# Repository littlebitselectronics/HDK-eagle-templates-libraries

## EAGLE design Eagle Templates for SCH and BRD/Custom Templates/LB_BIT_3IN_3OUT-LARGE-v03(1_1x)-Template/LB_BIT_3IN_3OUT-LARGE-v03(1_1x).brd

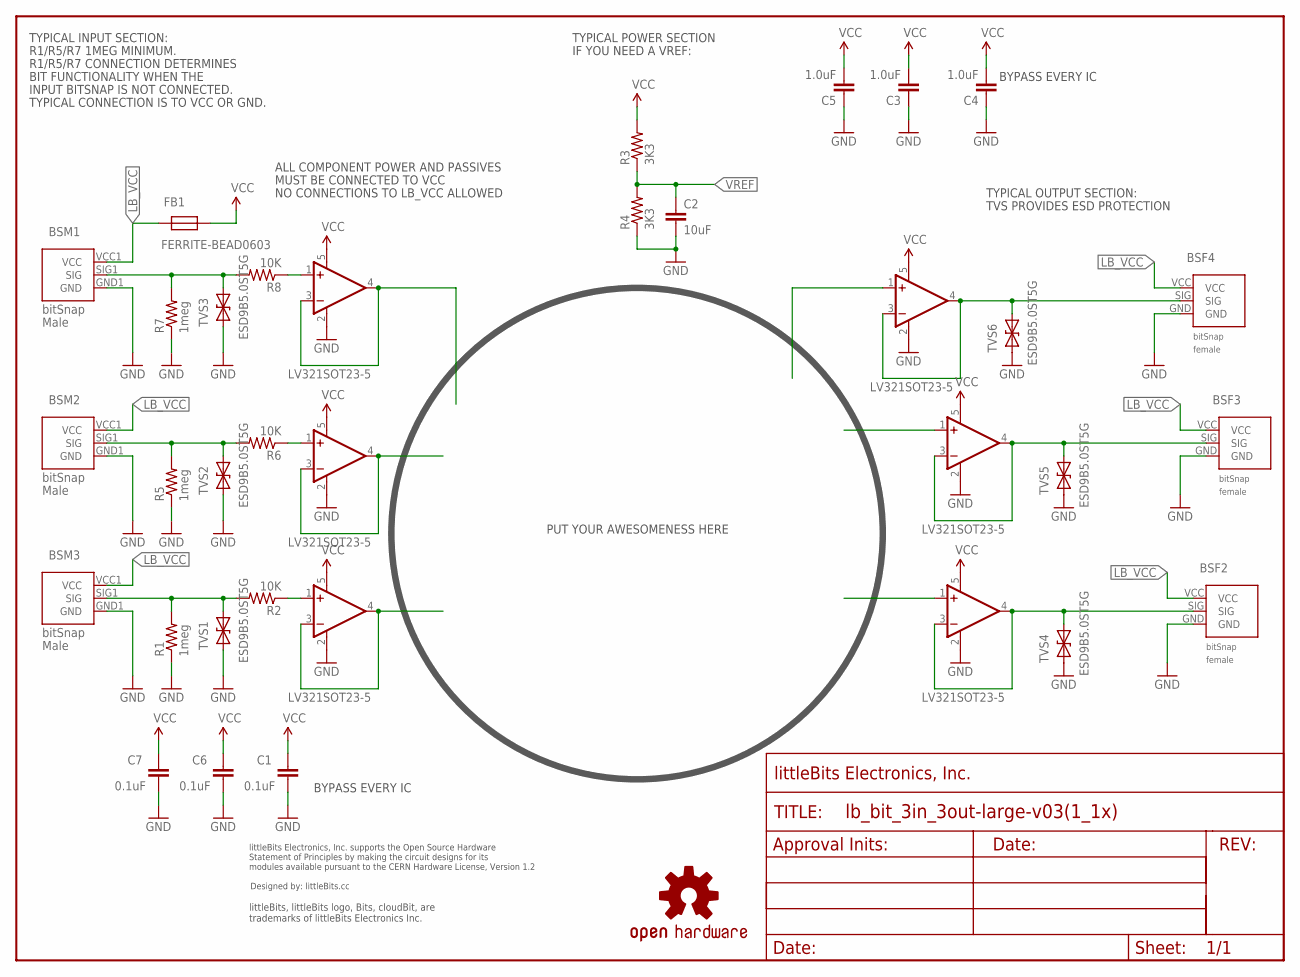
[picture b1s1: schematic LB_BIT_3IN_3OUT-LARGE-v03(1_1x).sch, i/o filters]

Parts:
BSF2, BSF3, BSF4: BITSNAP_V03_FEMALE
BSM1, BSM2, BSM3: BITSNAP_V03_MALE
C1, C6, C7: 0.1uF; CAP-0603
C2: 10uF; CAP-0603
C3, C4, C5: 1.0uF; CAP-0603
FB1: FERRITE-BEAD0603; R0603
FRAME1: FRAME-LETTER; FABDWG01-OHW
R1, R5, R7: 1meg; RES-0603
R2, R6, R8: 10K; RES-0603
R3, R4: 3K3; RES-0603
TVS1, TVS2, TVS3, TVS4, TVS5, TVS6: ESD9B5.0ST5G; SOD-923
U1, U2, U3, U4, U5, U6: LV321SOT23-5; SOT23-5
U$1: OSHWCREDIT
U$70: OSHW-LOGOL; OSHW-LOGO-L

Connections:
GND: BSF2.GND, BSF3.GND, BSF4.GND, BSM1.GND1 (GND), BSM2.GND1 (GND), BSM3.GND1 (GND), C1.2, C2.2, C3.1, C4.1, C5.1, C6.2, C7.2, R1.1, R4.1, R5.1, R7.1, TVS1.1 (A), TVS2.1 (A), TVS3.1 (A), TVS4.1 (A), TVS5.1 (A), TVS6.1 (A), U1.2 (V-), U2.2 (V-), U3.2 (V-), U4.2 (V-), U5.2 (V-), U6.2 (V-)
LB_VCC: BSF2.VCC, BSF3.VCC, BSF4.VCC, BSM1.VCC1 (VCC), BSM2.VCC1 (VCC), BSM3.VCC1 (VCC), FB1.2
unnamed: R2.1, U1.1 (+IN)
unnamed: U1.3 (-IN), U1.4 (OUT)
unnamed: BSM1.SIG1 (SIG), R7.2, R8.2, TVS3.2 (C)
unnamed: BSM2.SIG1 (SIG), R5.2, R6.2, TVS2.2 (C)
unnamed: BSM3.SIG1 (SIG), R1.2, R2.2, TVS1.2 (C)
unnamed: U2.3 (-IN), U2.4 (OUT)
unnamed: R6.1, U2.1 (+IN)
unnamed: U3.3 (-IN), U3.4 (OUT)
unnamed: R8.1, U3.1 (+IN)
SIG_OUT1: BSF4.SIG, TVS6.2 (C), U6.3 (-IN), U6.4 (OUT)
SIG_OUT2: BSF3.SIG, TVS5.2 (C), U5.3 (-IN), U5.4 (OUT)
SIG_OUT3: BSF2.SIG, TVS4.2 (C), U4.3 (-IN), U4.4 (OUT)
VCC: C1.1, C3.2, C4.2, C5.2, C6.1, C7.1, FB1.1, R3.2, U1.5 (V+), U2.5 (V+), U3.5 (V+), U4.5 (V+), U5.5 (V+), U6.5 (V+)
VREF: C2.1, R3.1, R4.2

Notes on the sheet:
R1/R5/R7 1MEG MINIMUM.
R1/R5/R7 CONNECTION DETERMINES
BIT FUNCTIONALITY WHEN THE
INPUT BITSNAP IS NOT CONNECTED.
TYPICAL CONNECTION IS TO VCC OR GND.
TYPICAL INPUT SECTION:
TYPICAL POWER SECTION
IF YOU NEED A VREF:
PUT YOUR AWESOMENESS HERE
TYPICAL OUTPUT SECTION:
BYPASS EVERY IC
NO CONNECTIONS TO LB_VCC ALLOWED
ALL COMPONENT POWER AND PASSIVES
MUST BE CONNECTED TO VCC
TVS PROVIDES ESD PROTECTION

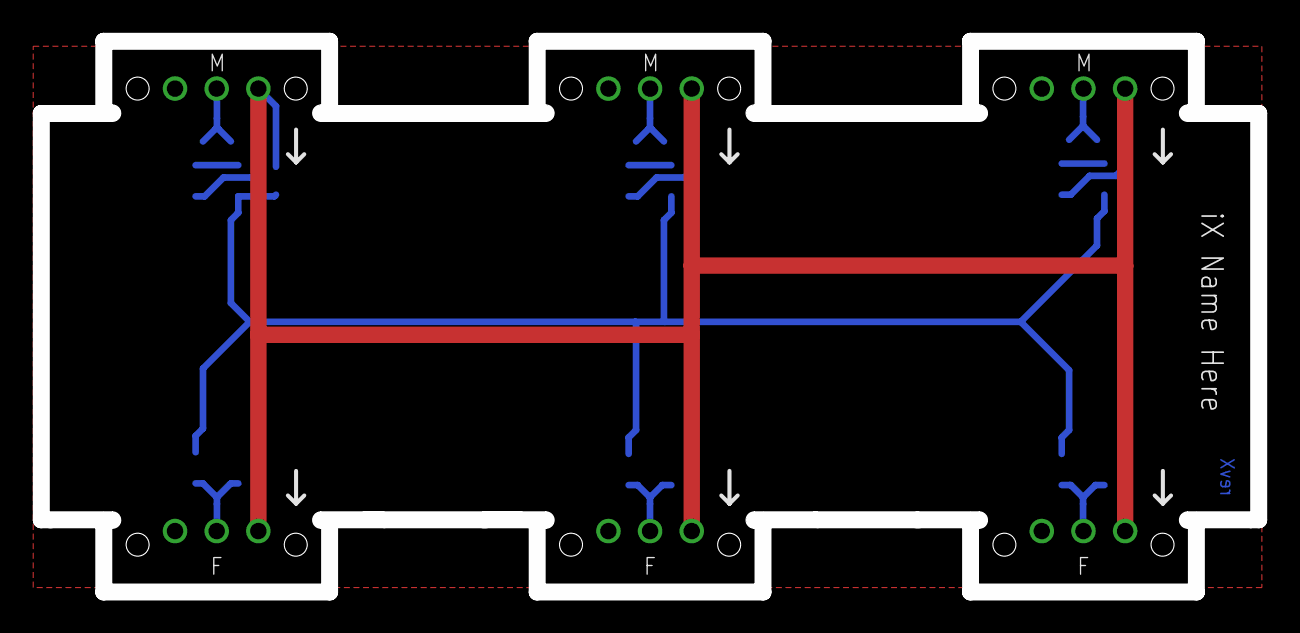
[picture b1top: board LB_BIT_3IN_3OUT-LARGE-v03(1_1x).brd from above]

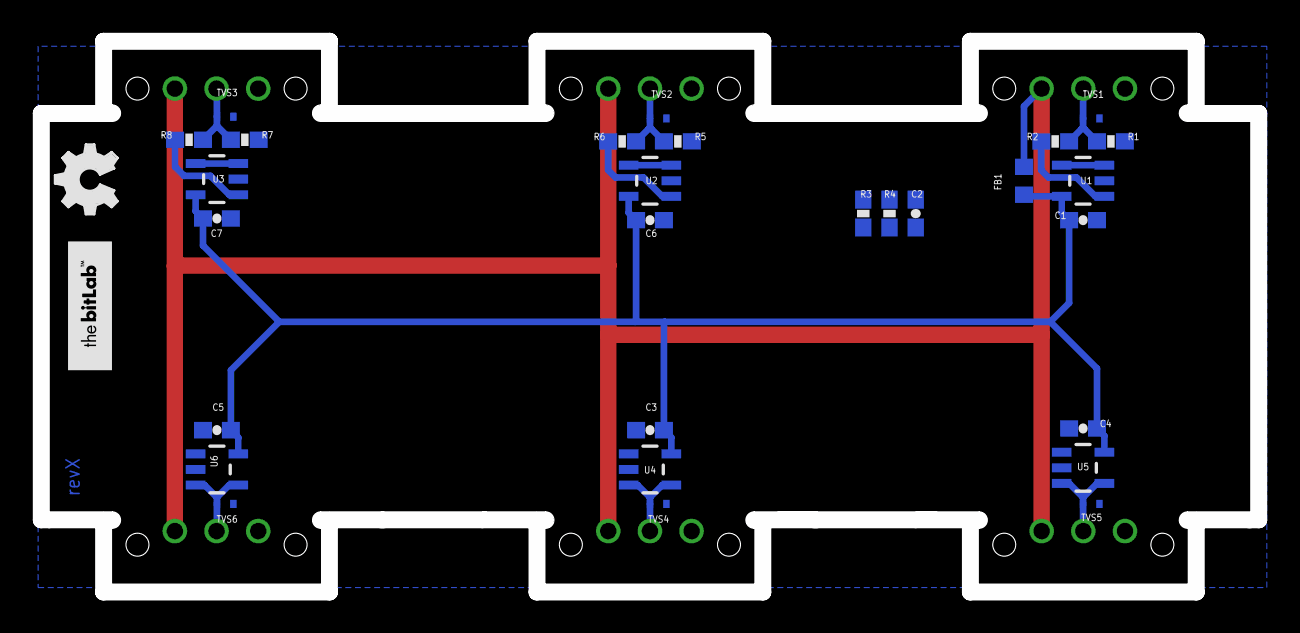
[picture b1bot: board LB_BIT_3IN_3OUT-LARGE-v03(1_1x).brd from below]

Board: 2 copper layers, 74.2 x 33.6 mm, 39 parts (28 on the bottom side), 16 nets.

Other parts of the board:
U$2: BITLAB-LOGO
U$5: OSHW_FILLX150_NOTEXT

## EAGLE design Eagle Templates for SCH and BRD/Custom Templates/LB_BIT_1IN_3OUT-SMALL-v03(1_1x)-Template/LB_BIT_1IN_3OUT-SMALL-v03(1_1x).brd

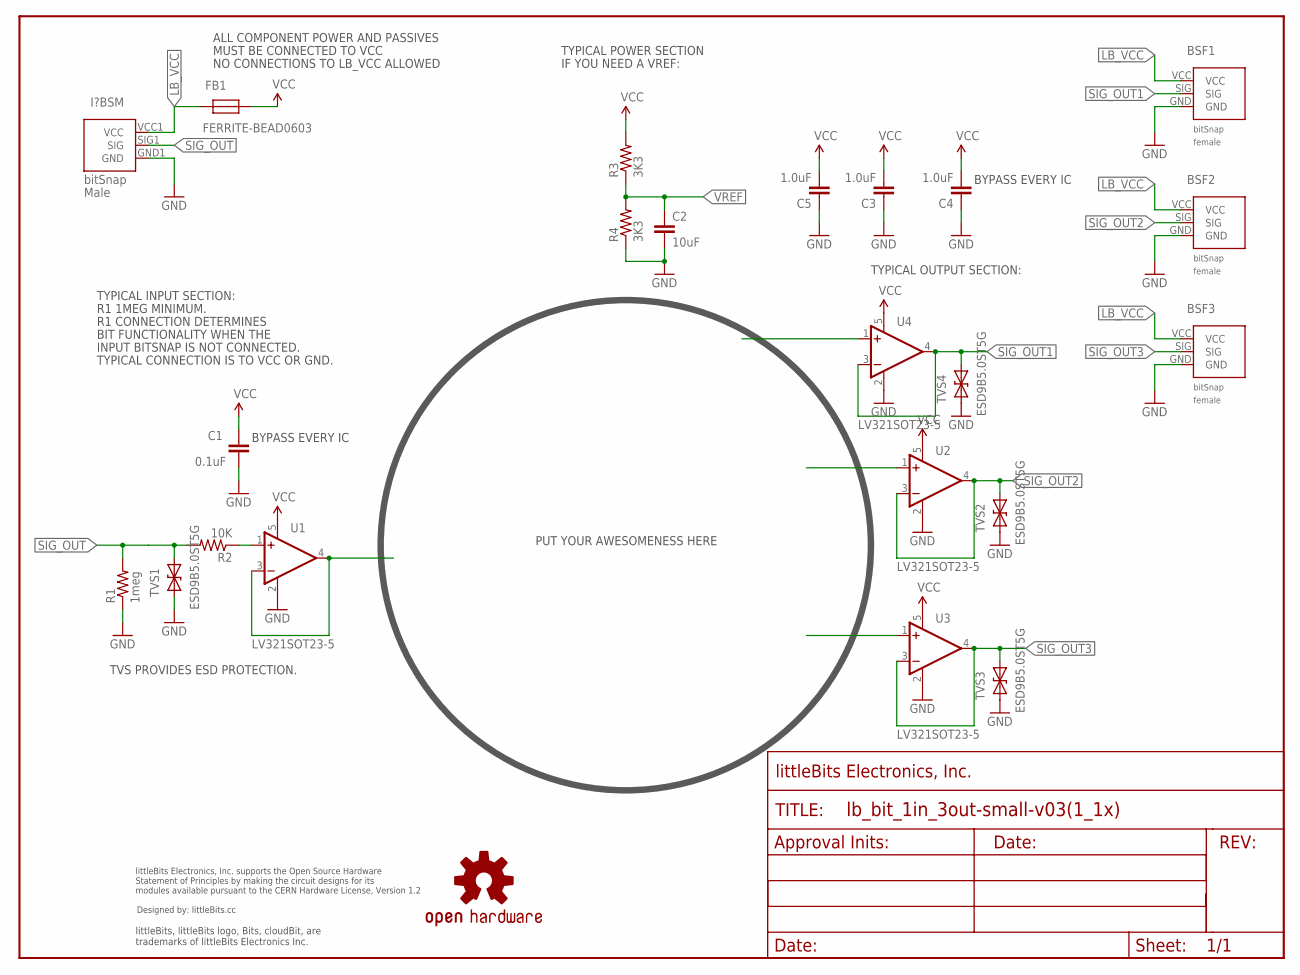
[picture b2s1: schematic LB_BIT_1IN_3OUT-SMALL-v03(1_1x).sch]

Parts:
BSF1, BSF2, BSF3: BITSNAP_V03_FEMALE
C1: 0.1uF; CAP-0603
C2: 10uF; CAP-0603
C3, C4, C5: 1.0uF; CAP-0603
FB1: FERRITE-BEAD0603; R0603
FRAME1: FRAME-LETTER; FABDWG01-OHW
I?BSM: BITSNAP_V03_MALE
R1: 1meg; RES-0603
R2: 10K; RES-0603
R3, R4: 3K3; RES-0603
TVS1, TVS2, TVS3, TVS4: ESD9B5.0ST5G; SOD-923
U1, U2, U3, U4: LV321SOT23-5; SOT23-5
U$1: OSHWCREDIT
U$3: OSHW-LOGOL; OSHW-LOGO-L

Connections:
GND: BSF1.GND, BSF2.GND, BSF3.GND, C1.2, C2.2, C3.1, C4.1, C5.1, I?BSM.GND1 (GND), R1.1, R4.1, TVS1.1 (A), TVS2.1 (A), TVS3.1 (A), TVS4.1 (A), U1.2 (V-), U2.2 (V-), U3.2 (V-), U4.2 (V-)
LB_VCC: BSF1.VCC, BSF2.VCC, BSF3.VCC, FB1.2, I?BSM.VCC1 (VCC)
unnamed: U1.3 (-IN), U1.4 (OUT)
unnamed: R2.1, U1.1 (+IN)
SIG_OUT: I?BSM.SIG1 (SIG), R1.2, R2.2, TVS1.2 (C)
SIG_OUT1: BSF1.SIG, TVS4.2 (C), U4.3 (-IN), U4.4 (OUT)
SIG_OUT2: BSF2.SIG, TVS2.2 (C), U2.3 (-IN), U2.4 (OUT)
SIG_OUT3: BSF3.SIG, TVS3.2 (C), U3.3 (-IN), U3.4 (OUT)
VCC: C1.1, C3.2, C4.2, C5.2, FB1.1, R3.2, U1.5 (V+), U2.5 (V+), U3.5 (V+), U4.5 (V+)
VREF: C2.1, R3.1, R4.2

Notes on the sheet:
R1 1MEG MINIMUM.
R1 CONNECTION DETERMINES
BIT FUNCTIONALITY WHEN THE
INPUT BITSNAP IS NOT CONNECTED.
TYPICAL CONNECTION IS TO VCC OR GND.
TVS PROVIDES ESD PROTECTION.
TYPICAL INPUT SECTION:
TYPICAL POWER SECTION
IF YOU NEED A VREF:
PUT YOUR AWESOMENESS HERE
BYPASS EVERY IC
NO CONNECTIONS TO LB_VCC ALLOWED
ALL COMPONENT POWER AND PASSIVES
MUST BE CONNECTED TO VCC
TYPICAL OUTPUT SECTION:

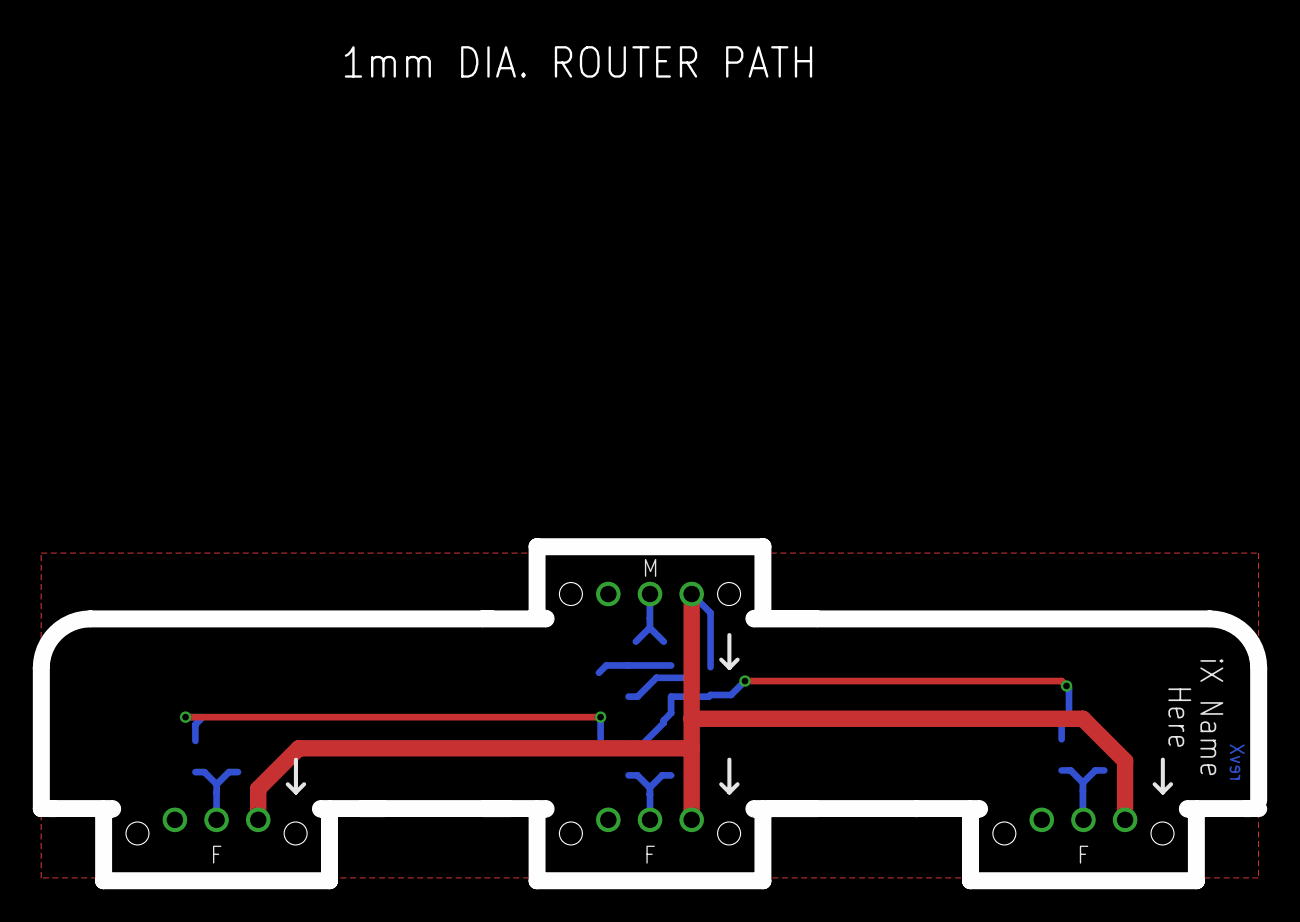
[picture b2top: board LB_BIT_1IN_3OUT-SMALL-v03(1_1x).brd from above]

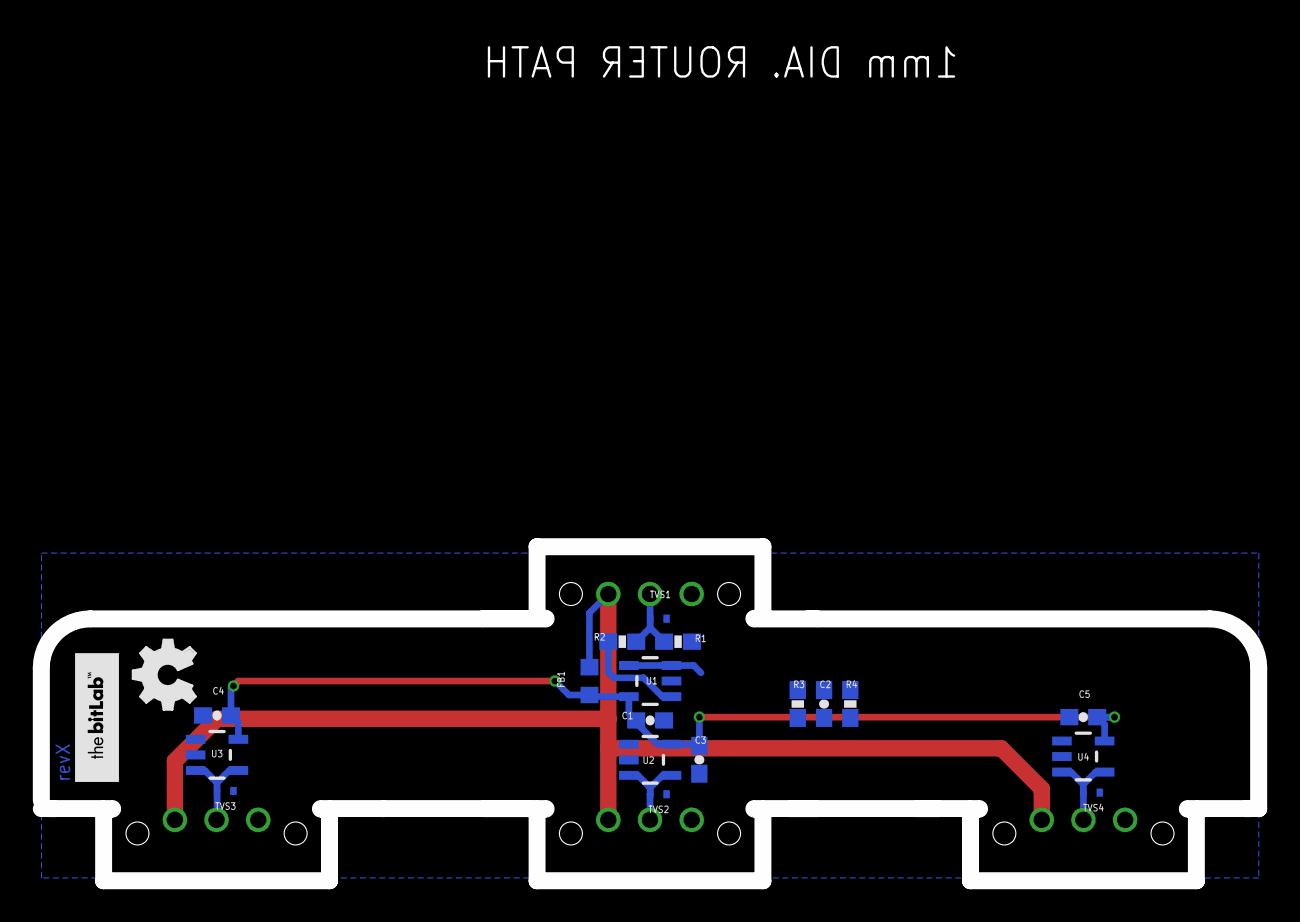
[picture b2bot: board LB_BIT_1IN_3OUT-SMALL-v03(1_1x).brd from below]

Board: 2 copper layers, 74.2 x 51.2 mm, 27 parts (18 on the bottom side), 10 nets.

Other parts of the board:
U$2: BITLAB-LOGO
U$8: OSHW_FILLX150_NOTEXT

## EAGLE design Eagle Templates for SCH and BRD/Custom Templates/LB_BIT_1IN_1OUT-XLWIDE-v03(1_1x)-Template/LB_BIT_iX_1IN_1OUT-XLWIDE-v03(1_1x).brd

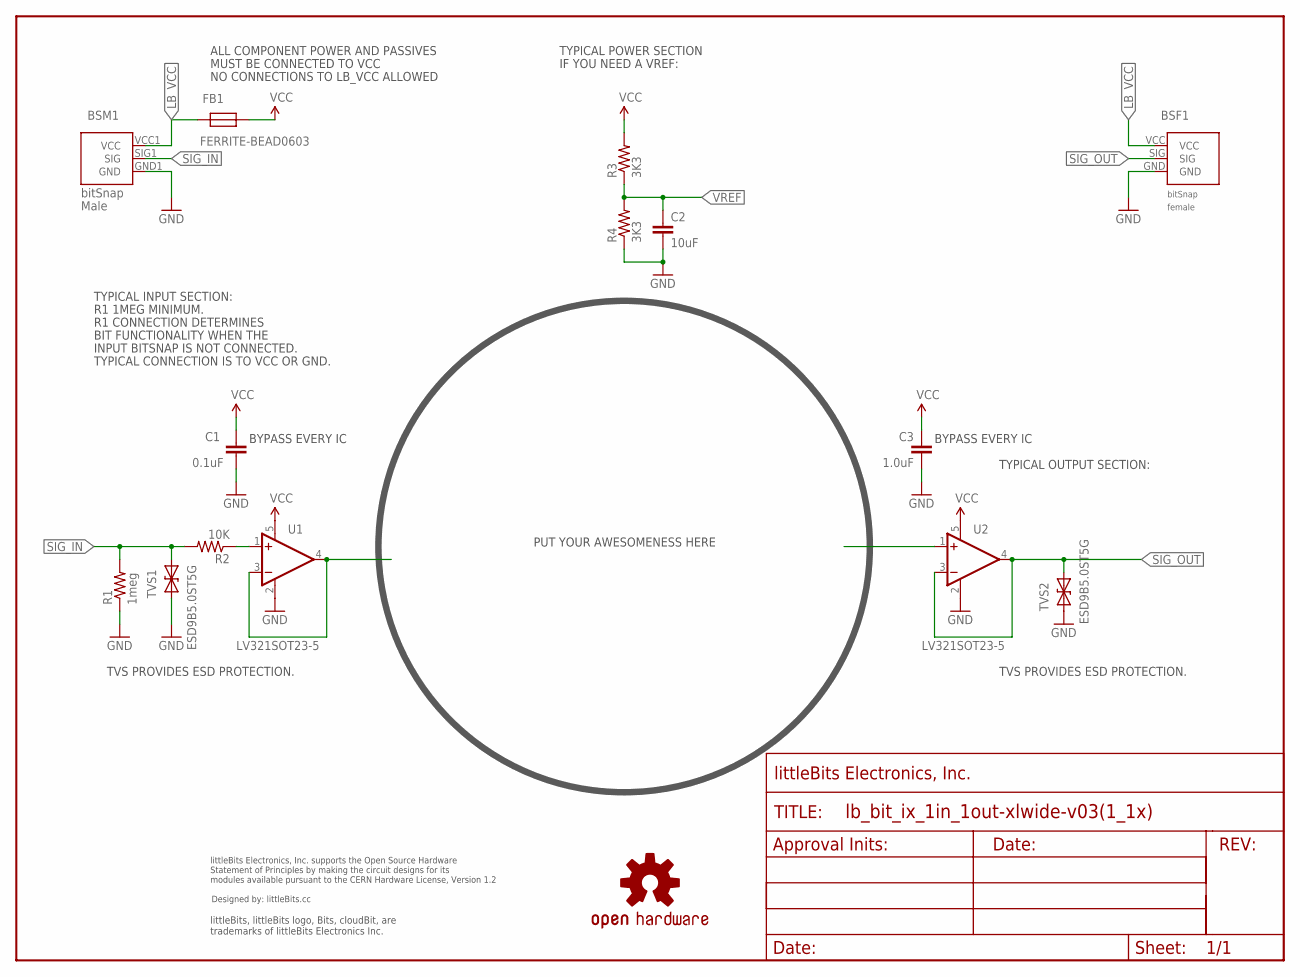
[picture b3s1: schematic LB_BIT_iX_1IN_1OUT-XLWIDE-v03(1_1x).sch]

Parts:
BSF1: BITSNAP_V03_FEMALE
BSM1: BITSNAP_V03_MALE
C1: 0.1uF; CAP-0603
C2: 10uF; CAP-0603
C3: 1.0uF; CAP-0603
FB1: FERRITE-BEAD0603; R0603
R1: 1meg; RES-0603
R2: 10K; RES-0603
R3, R4: 3K3; RES-0603
TVS1, TVS2: ESD9B5.0ST5G; SOD-923
U1, U2: LV321SOT23-5; SOT23-5
U$1: OSHW-LOGOL; OSHW-LOGO-L
U$2: OSHWCREDIT
U$5: FRAME-LETTER-OHWOHW; FABDWG01-OHW

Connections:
GND: BSF1.GND, BSM1.GND1 (GND), C1.2, C2.2, C3.1, R1.1, R4.1, TVS1.1 (A), TVS2.1 (A), U1.2 (V-), U2.2 (V-)
LB_VCC: BSF1.VCC, BSM1.VCC1 (VCC), FB1.2
unnamed: U1.3 (-IN), U1.4 (OUT)
unnamed: R2.1, U1.1 (+IN)
SIG_IN: BSM1.SIG1 (SIG), R1.2, R2.2, TVS1.2 (C)
SIG_OUT: BSF1.SIG, TVS2.2 (C), U2.3 (-IN), U2.4 (OUT)
VCC: C1.1, C3.2, FB1.1, R3.2, U1.5 (V+), U2.5 (V+)
VREF: C2.1, R3.1, R4.2

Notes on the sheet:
R1 1MEG MINIMUM.
R1 CONNECTION DETERMINES
BIT FUNCTIONALITY WHEN THE
INPUT BITSNAP IS NOT CONNECTED.
TYPICAL CONNECTION IS TO VCC OR GND.
TVS PROVIDES ESD PROTECTION.
TYPICAL INPUT SECTION:
TYPICAL POWER SECTION
IF YOU NEED A VREF:
TYPICAL OUTPUT SECTION:
PUT YOUR AWESOMENESS HERE
BYPASS EVERY IC
NO CONNECTIONS TO LB_VCC ALLOWED
ALL COMPONENT POWER AND PASSIVES
MUST BE CONNECTED TO VCC

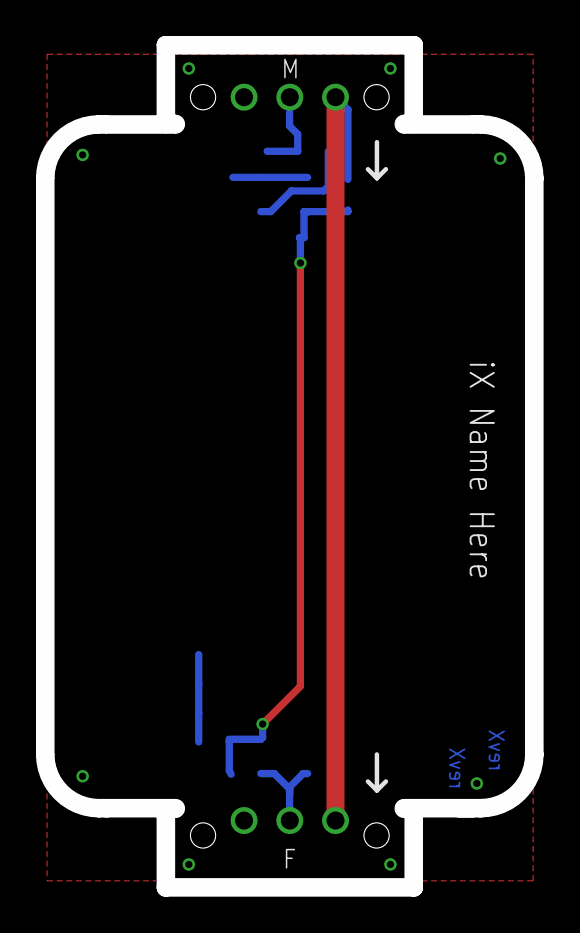
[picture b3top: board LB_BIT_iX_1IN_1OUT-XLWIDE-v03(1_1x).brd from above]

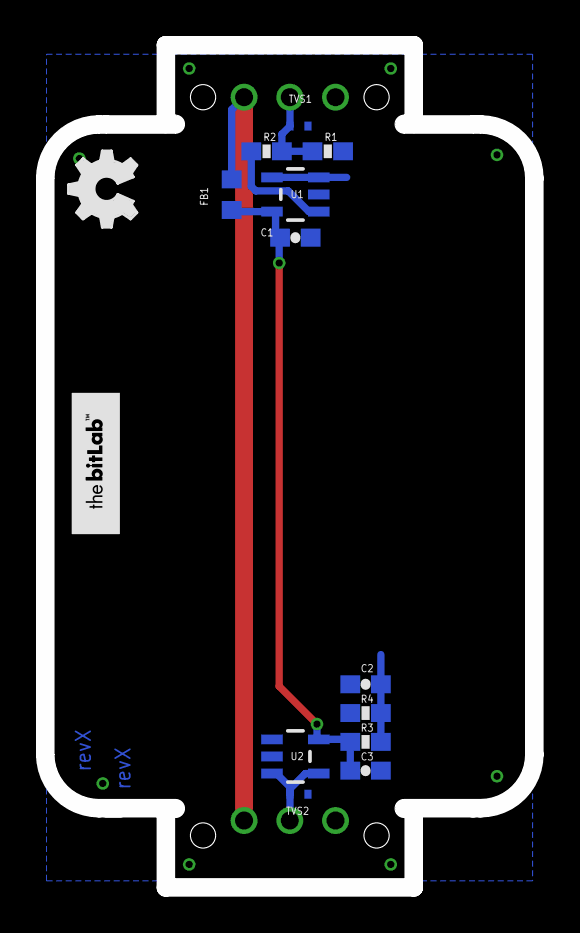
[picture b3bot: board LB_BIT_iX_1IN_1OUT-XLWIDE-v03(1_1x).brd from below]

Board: 2 copper layers, 27.2 x 46.8 mm, 19 parts (13 on the bottom side), 8 nets.

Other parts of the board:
U$3: OSHW_FILLX150_NOTEXT
U$4: BITLAB-LOGO

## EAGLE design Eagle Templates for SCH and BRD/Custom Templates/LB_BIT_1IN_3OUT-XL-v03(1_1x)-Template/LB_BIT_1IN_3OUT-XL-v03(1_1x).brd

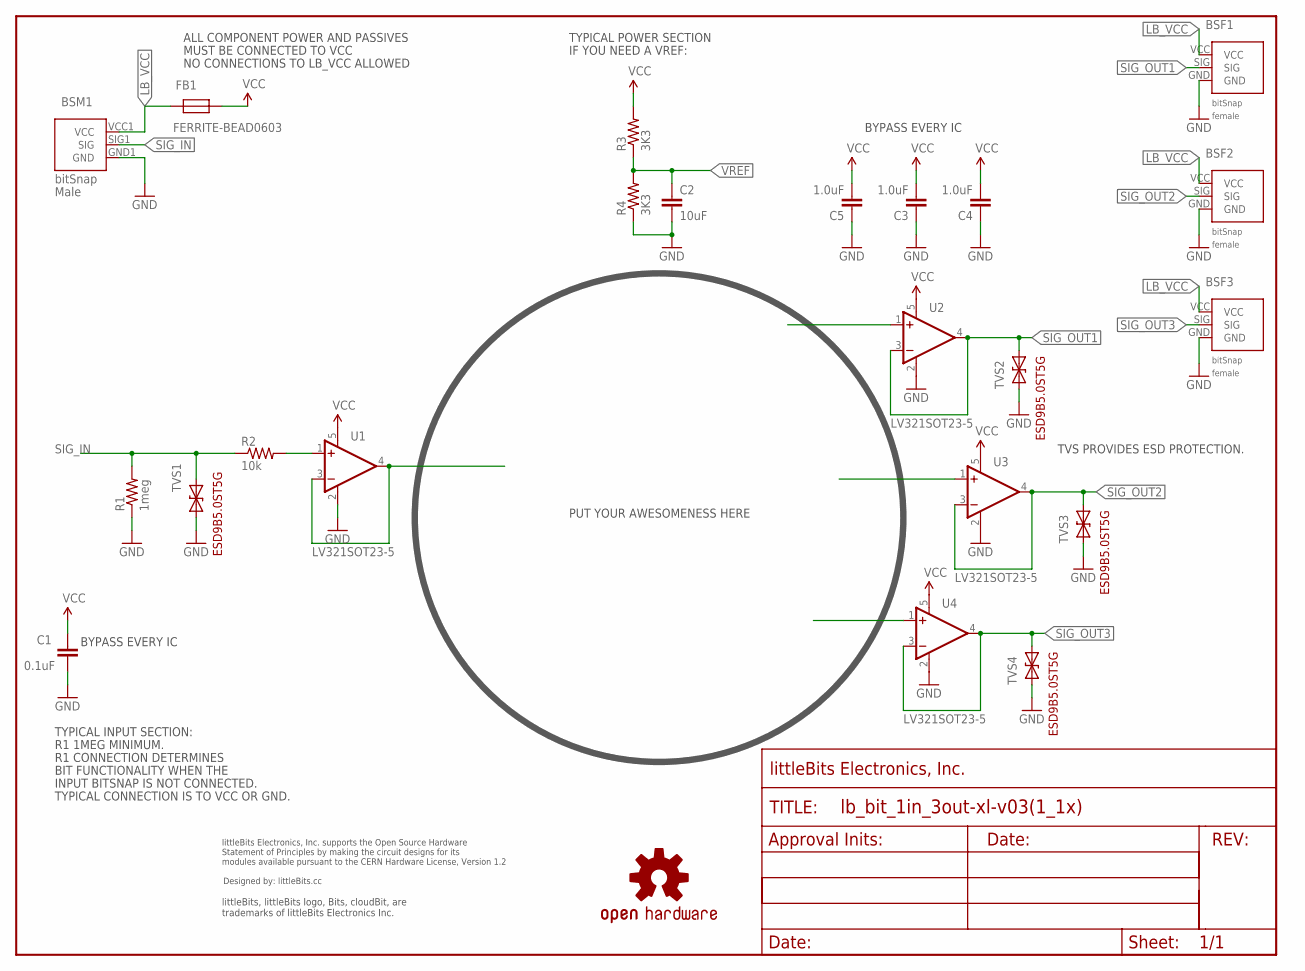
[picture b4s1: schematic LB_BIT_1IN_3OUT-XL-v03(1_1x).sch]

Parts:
BSF1, BSF2, BSF3: BITSNAP_V03_FEMALE
BSM1: BITSNAP_V03_MALE
C1: 0.1uF; CAP-0603
C2: 10uF; CAP-0603
C3, C4, C5: 1.0uF; CAP-0603
FB1: FERRITE-BEAD0603; R0603
FRAME1: FRAME-LETTER; FABDWG01-OHW
R1: 1meg; RES-0603
R2: 10k; RES-0603
R3, R4: 3K3; RES-0603
TVS1, TVS2, TVS3, TVS4: DIODE-TVSSOD-923; SOD-923
U1, U2, U3, U4: LV321SOT23-5; SOT23-5
U$1: OSHWCREDIT
U$6: OSHW-LOGOL; OSHW-LOGO-L

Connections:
GND: BSF1.GND, BSF2.GND, BSF3.GND, BSM1.GND1 (GND), C1.2, C2.2, C3.1, C4.1, C5.1, R1.1, R4.1, TVS1.1 (A), TVS2.1 (A), TVS3.1 (A), TVS4.1 (A), U1.2 (V-), U2.2 (V-), U3.2 (V-), U4.2 (V-)
LB_VCC: BSF1.VCC, BSF2.VCC, BSF3.VCC, BSM1.VCC1 (VCC), FB1.2
unnamed: U1.3 (-IN), U1.4 (OUT)
unnamed: R2.2, U1.1 (+IN)
SIG_IN: BSM1.SIG1 (SIG), R1.2, R2.1, TVS1.2 (C)
SIG_OUT1: BSF1.SIG, TVS2.2 (C), U2.3 (-IN), U2.4 (OUT)
SIG_OUT2: BSF2.SIG, TVS3.2 (C), U3.3 (-IN), U3.4 (OUT)
SIG_OUT3: BSF3.SIG, TVS4.2 (C), U4.3 (-IN), U4.4 (OUT)
VCC: C1.1, C3.2, C4.2, C5.2, FB1.1, R3.2, U1.5 (V+), U2.5 (V+), U3.5 (V+), U4.5 (V+)
VREF: C2.1, R3.1, R4.2

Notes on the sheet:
R1 1MEG MINIMUM.
R1 CONNECTION DETERMINES
BIT FUNCTIONALITY WHEN THE
INPUT BITSNAP IS NOT CONNECTED.
TYPICAL CONNECTION IS TO VCC OR GND.
TYPICAL INPUT SECTION:
TYPICAL POWER SECTION
IF YOU NEED A VREF:
PUT YOUR AWESOMENESS HERE
BYPASS EVERY IC
TVS PROVIDES ESD PROTECTION.
NO CONNECTIONS TO LB_VCC ALLOWED
ALL COMPONENT POWER AND PASSIVES
MUST BE CONNECTED TO VCC

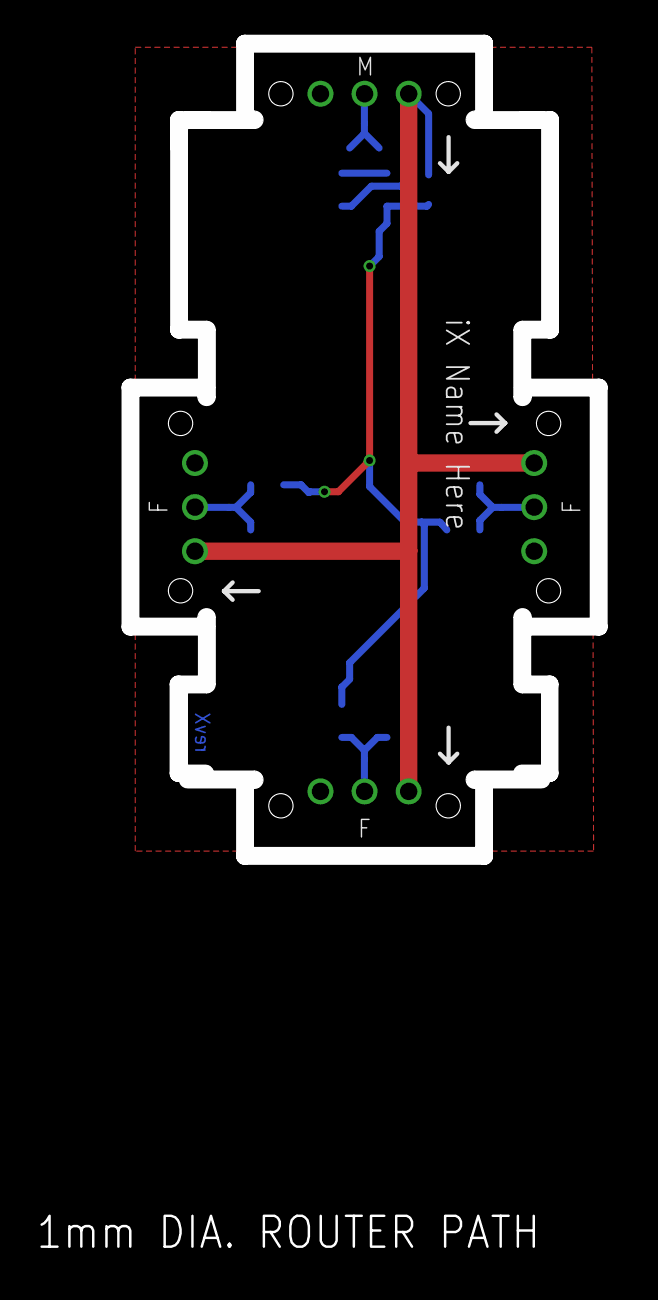
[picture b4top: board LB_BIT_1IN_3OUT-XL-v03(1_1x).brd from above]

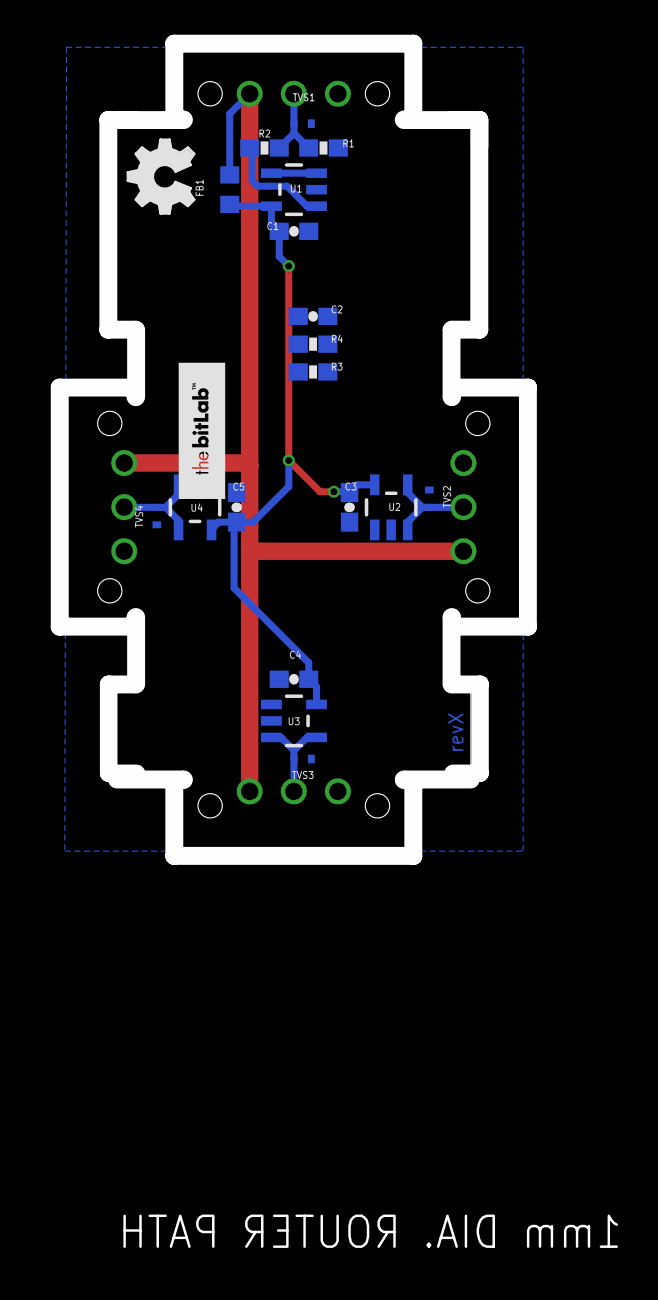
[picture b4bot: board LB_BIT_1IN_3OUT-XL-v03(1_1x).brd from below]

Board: 2 copper layers, 32.9 x 69.9 mm, 27 parts (18 on the bottom side), 10 nets.

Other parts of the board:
U$2: BITLAB-LOGO
U$5: OSHW_FILLX150_NOTEXT

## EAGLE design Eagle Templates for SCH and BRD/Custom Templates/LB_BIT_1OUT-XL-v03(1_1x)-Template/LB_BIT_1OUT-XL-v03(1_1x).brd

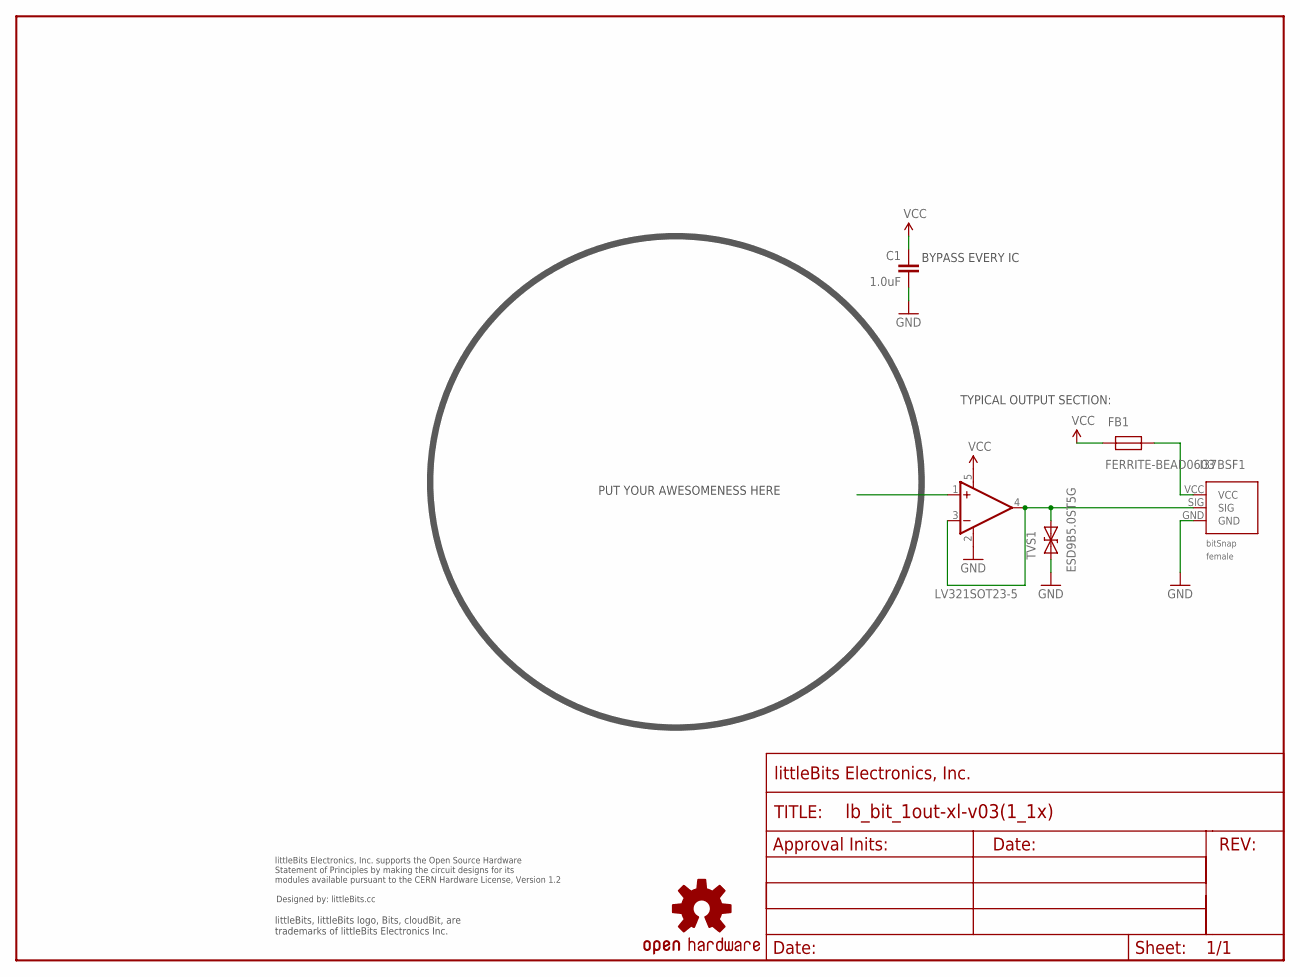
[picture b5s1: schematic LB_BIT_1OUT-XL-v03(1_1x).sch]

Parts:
C1: 1.0uF; CAP-0603
FB1: FERRITE-BEAD0603; R0603
FRAME1: FRAME-LETTERWHITEMASK; FABDWG01-WHITEMASK
I37BSF1: BITSNAP_V03_FEMALE
TVS1: ESD9B5.0ST5G; SOD-923
U1: LV321SOT23-5; SOT23-5
U$1: OSHWCREDIT
U$3: OSHW-LOGOL; OSHW-LOGO-L

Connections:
GND: C1.1, I37BSF1.GND, TVS1.1 (A), U1.2 (V-)
unnamed: FB1.1, I37BSF1.VCC
SIG_OUT: I37BSF1.SIG, TVS1.2 (C), U1.3 (-IN), U1.4 (OUT)
VCC: C1.2, FB1.2, U1.5 (V+)

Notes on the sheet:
PUT YOUR AWESOMENESS HERE
TYPICAL OUTPUT SECTION:
BYPASS EVERY IC

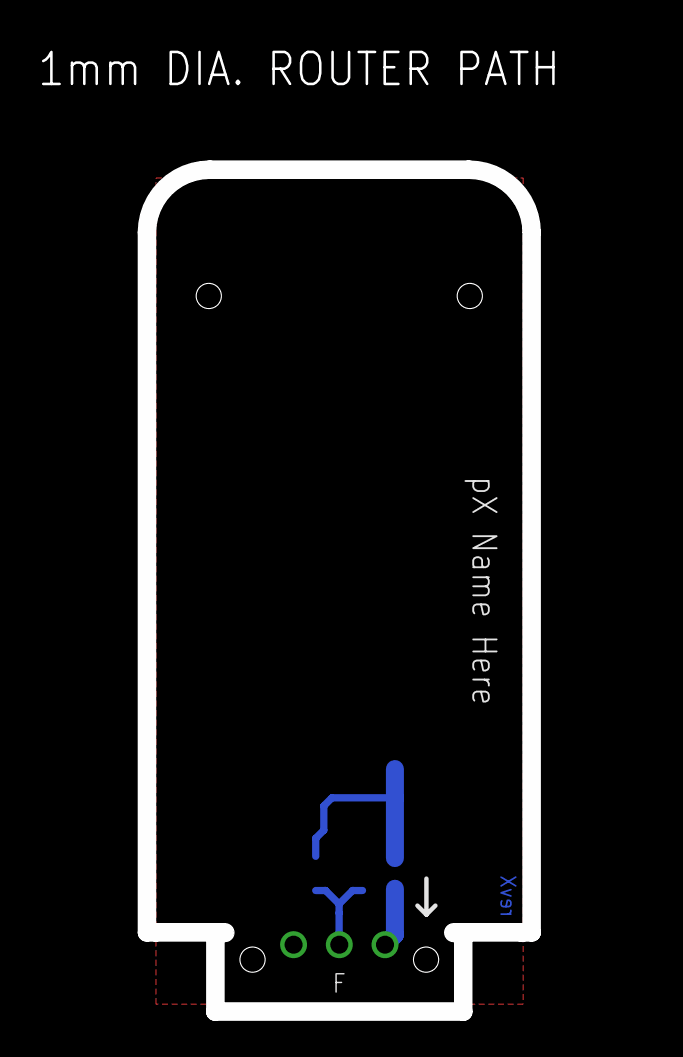
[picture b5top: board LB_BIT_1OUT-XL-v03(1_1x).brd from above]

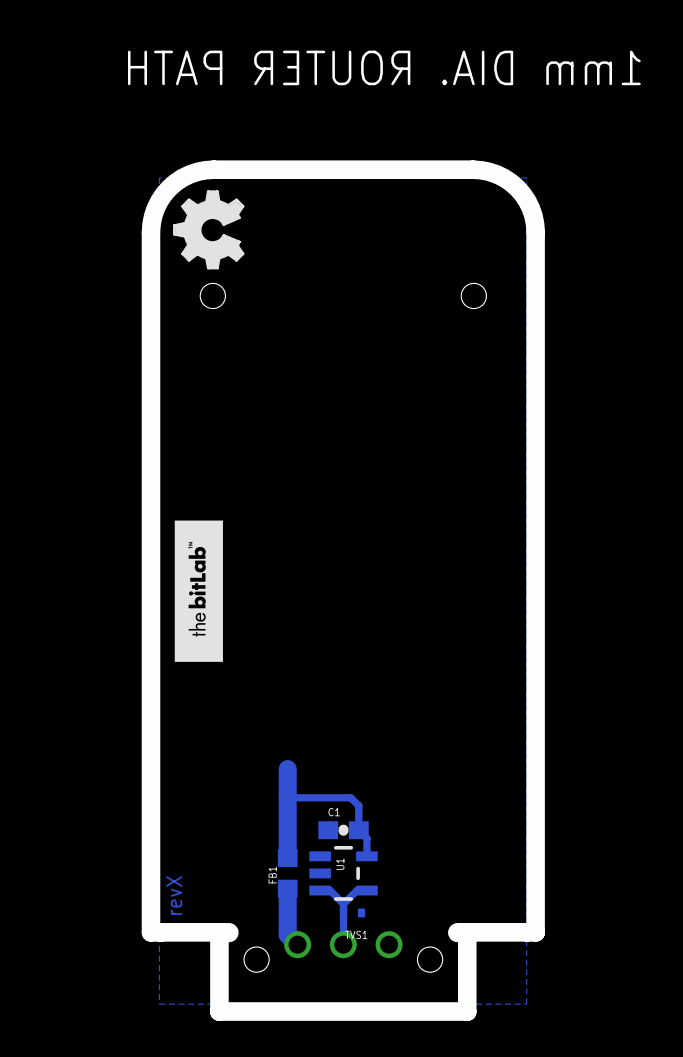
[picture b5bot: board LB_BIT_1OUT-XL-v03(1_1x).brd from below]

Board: 2 copper layers, 32.9 x 53.7 mm, 11 parts (4 on the bottom side), 4 nets.

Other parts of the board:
U$2: BITLAB-LOGO
U$4: LB_PWR_LEGS
U$8: OSHW_FILLX150_NOTEXT

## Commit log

2014-09-08 Added templates and libraries.
2014-09-11 Deleted eagle save backups
2014-09-15 added bitlab logo and made minor changes to board templates. Updated littlebits library.
2014-09-15 Updated littlebits library
2014-10-10 Fixed input and output bitsnap connections
2014-12-03 Moved output stages which were placed next to the wrong bitsnaps
2014-12-12 Moved vref
    Test
2015-01-14 Updated templates
    - Added ferrite beads
    - Moved text and annotations off of Nets layer
    - Minor layout changes
    - Removed I/O/W prefix from reference designators
    - Removed output stage components from output bits

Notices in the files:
parts and their libraries:
LITTLEBITS: modules available pursuant to the CERN Hardware License,
Version 1.2
LITTLEBITS: modules available pursuant to the CERN Hardware License, Version 1.2
SparkFun_NEW: Licensing: CC v3.0 Share-Alike You are welcome to use this library for commercial purposes.
